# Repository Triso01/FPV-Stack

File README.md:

# My FPV Stack

Note:
  I made it because I want to learn how to make BLDC-ESCs, 
  Designing my own FPV Stack, it WILL have errors, so do NOT use it in your Drone!
  The 4 in 1 ESC will be continued later, I don not have the experience to finish it yet.
  
## Flight Controller:

- No Analog OSD, made for BetaFPV P1 or optionally Walksnail and DJI
- BEC: 5V 3A; 9V 3A
- IMU (Gyro): ICM-20602
- STM32F405
- Buzzer Pads
- 1 UART free to use e.g. for GPS

ESC and Flight Controller Connector Pinout:

| [1]  | [2] | [3]  | [4]  | [5] | [6] | [7] | [8] |
|------|-----|------|------|-----|-----|-----|-----|
| VBAT | GND | CUR  | TEL  | M1  | M2  | M3  | M4  |

VTX Connector Pinout:

| [1] | [2] | [3]  | [4]   | [5] | [6] |
|-----|-----|------|-------|-----|-----|
| 5V  | GND | U1_TX| U1_RX | GND | NC  |

## ESCs:
Based on EFM88B21, FD6288 and PSMN1R4-40YLDX.
  - Bluejay (Layout A), BLHeli_S compatible
  - Dshot bidirectional

## ESC distribution board:
10V Buck, 3,3V LDO and the ampmeter

[Will be finished, when I have more experience]:
4in1 ESC:
Based on EFM8BB21, FD6288Q and 24 PSMN1R4-40YLDX.
The PCB size is not final yet, it WILL change.
  - Bluejay (Laout A), BLHeli_S compatible
  - Dshot bidirectional compatible
  - Current Sensor: INA168 with a 0.5mOhms shunt
  - LMR14010 10V Buck to provide Gate voltage
  - AP2204K LDO 10V -> 3.3V
(You can see "pictures" when opening the PCB Files with KiCad)

## What are the boards for?

The Flight Controller (FC) is the main control board and the "brain" of the FPV stack. It runs the flight-control firmware and uses its IMU to measure the drone's movement, which is required for stable flight.

The ESC Distribution Board distributes one battery connection to four individual ESCs. It also generates the 10 V gate-driver supply, and measures the total battery current.

Each Electronic Speed Controller (ESC) drives one three-phase brushless motor. Designing this small, high-current board was the most challenging part of the project.

## Now the expensive things (duhhh):

PCBs:

Settings for FC:

Settings for ESC:

Settings for ESC-Distrib:

(You can change Surface Finish and Color if you want another Color or a higher quality finish)

Parts:
1. Select the columns like this
2. Click "Create BOM"

3. Click on "Add to Cart"

## Grouped BOM

| Part group | Qty used | Price (USD) |
|---|---:|---:|
| Resistors, including the current shunt | 68 | $3.09 |
| Capacitors | 85 | $9.99 |
| Inductors | 3 | $2.40 |
| Semiconductors and ICs | 57 | $73.05 |
| USB receptacle | 1 | $1.50 |
| Switches | 2 | $0.53 |
| Cables | 6 | $0.00 |
| PCBs | 6 | $103.30 |
| Shipping | 1-2 | ~$20-40 |
| **Total** | | **$195.79** |

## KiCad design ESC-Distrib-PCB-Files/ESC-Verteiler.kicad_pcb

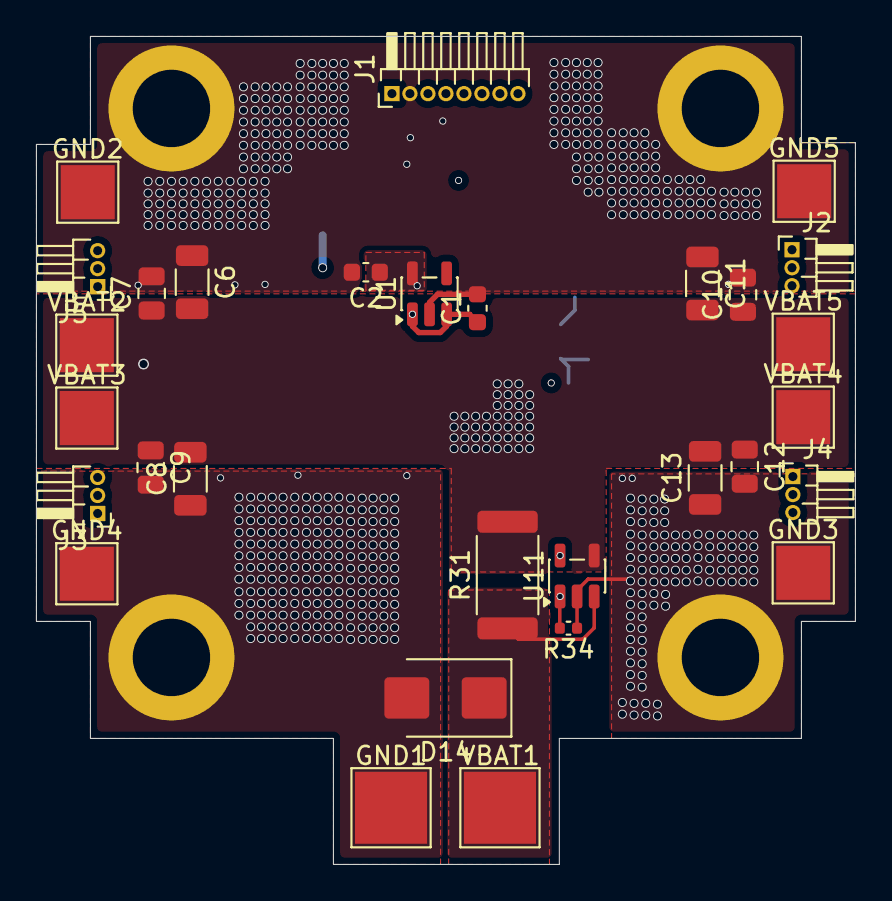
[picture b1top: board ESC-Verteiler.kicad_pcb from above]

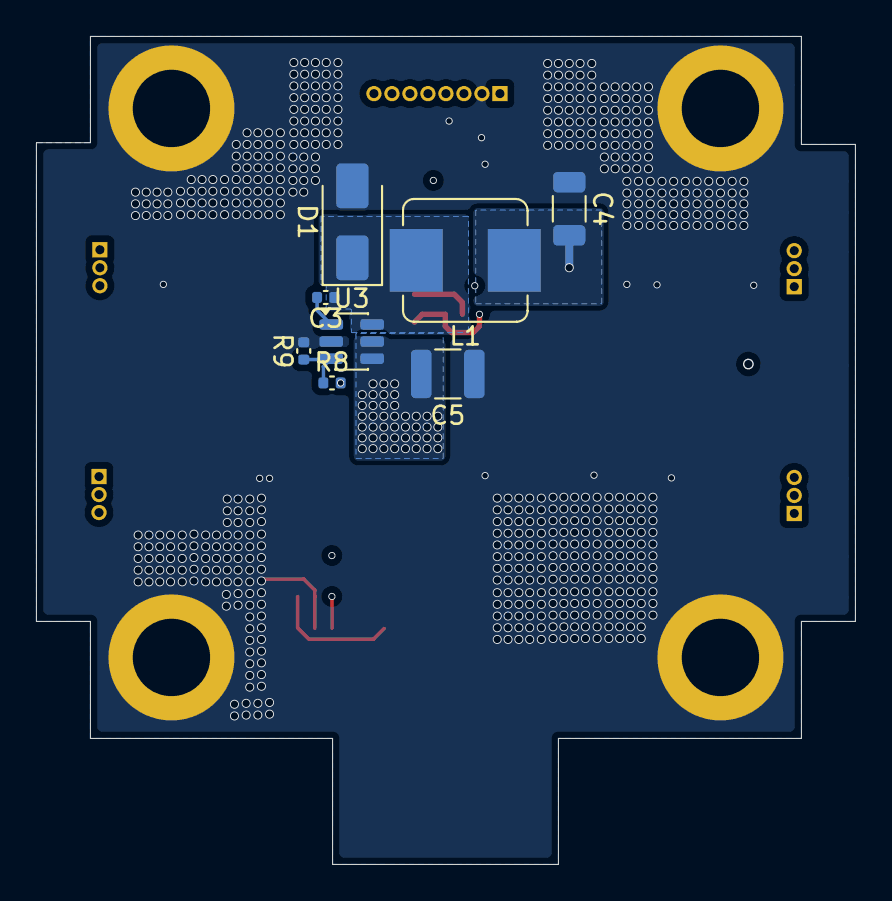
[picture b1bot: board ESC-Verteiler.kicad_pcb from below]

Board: 4 copper layers, 45.5 x 46.0 mm, 38 parts (8 on the bottom side), 13 nets.

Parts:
C1: 1uf; C_0603_1608Metric
C2: 2.2uf; C_0603_1608Metric
C3: 100nf; C_0402_1005Metric
C4: 22uf; C_1206_3216Metric
C5: 10uf; C_1210_3225Metric
C6, C8, C11, C13: 1uf; C_1206_3216Metric
C7, C9, C10, C12: 100nf; C_0805_2012Metric
D1: D; D_SMA
D14: D; D_SMB
GND1: TestPoint_Pad_4.0x4.0mm
GND2, GND3, GND4, GND5: TestPoint_Pad_3.0x3.0mm
J1: Conn_01x08_Socket; PinHeader_1x08_P1.00mm_Horizontal
J2, J3, J4, J5: Conn_01x03_Pin; PinHeader_1x03_P1.00mm_Horizontal
L1: 22uH; L_Bourns_SRP7028A_7.3x6.6mm
R8: 121kOhm; C_0402_1005Metric
R9: 10kOhm; C_0402_1005Metric
R31: 0.5mOhms; R_2512_6332Metric
R34: 200kOhm; C_0402_1005Metric
U1: AP2204K-3.3; SOT-23-5
U3: LMR14010ADDCT; SOT-23-6
U11: INA168; SOT-23-5
VBAT1: TestPoint_Pad_4.0x4.0mm
VBAT2, VBAT3, VBAT4, VBAT5: TestPoint_Pad_3.0x3.0mm

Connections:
/10V: C1.1, C4.2, J2.1, J3.3, J4.1, J5.3, L1.1, R8.2, U1.1 (VIN), U1.3 (EN)
/CUR: J1.3, R34.2, U11.1
/DSHOT_M1: J1.8, J3.2
/DSHOT_M2: J1.7, J5.2
/DSHOT_M3: J1.6, J2.2
/DSHOT_M4: J1.5, J4.2
/GND: C1.2, C2.2, C4.1, C5.1, C6.1, C7.2, C8.1, C9.2, C10.2, C11.1, C12.2, C13.1, D1.2 (A), D14.2 (A), GND1.1 (1_1), GND2.1 (1_1), GND3.1 (1_1), GND4.1 (1_1), GND5.1 (1_1), J1.2, R9.2, R34.1, U1.2 (GND), U3.2 (GND), U11.2 (GND)
/VBAT: C5.2, C6.2, C7.1, C8.2, C9.1, C10.1, C11.2, C12.1, C13.2, J1.1, R31.2, U3.4 (SHDN), U3.5 (VIN), U11.4 (-), VBAT2.1 (1_1), VBAT3.1 (1_1), VBAT4.1 (1_1), VBAT5.1 (1_1)
/VDD: C2.1, J2.3, J3.1, J4.3, J5.1, U1.5 (VOUT), U11.5 (V+)
unnamed: C3.1, D1.1 (K), L1.2, U3.6 (SW)
unnamed: D14.1 (K), R31.1, U11.3 (+), VBAT1.1 (1_1)
unnamed: C3.2, U3.1 (CB)
unnamed: R8.1, R9.1, U3.3 (FB)

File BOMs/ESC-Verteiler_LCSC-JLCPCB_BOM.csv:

"Comment","Designator","Footprint","Quantity","LCSC Part #"
"1uf","C1","Capacitor_SMD:C_0603_1608Metric","1","C15849"
"2.2uf","C2","Capacitor_SMD:C_0603_1608Metric","1","C23630"
"100nf","C3","Capacitor_SMD:C_0402_1005Metric","1","C960916"
"22uf","C4","Capacitor_SMD:C_1206_3216Metric","1","C2858005"
"10uf","C5","Capacitor_SMD:C_1210_3225Metric","1","C342670"
"1uf","C6,C8,C11,C13","Capacitor_SMD:C_1206_3216Metric","4","C1853626"
"100nf","C7,C9,C10,C12","Capacitor_SMD:C_0805_2012Metric","4","C1711"
"D","D1","Diode_SMD:D_SMA","1","C169419"
"D","D14","Diode_SMD:D_SMB","1","C726831"
"JST SH 1.0mm Horizontal 8P","J1","Connector_JST:JST_SH_SM08B-SRSS-TB_1x08-1MP_P1.00mm_Horizontal","1","C160407"
"JST SH 1.0mm Horizontal 3P","J2,J3,J4,J5","Connector_JST:JST_SH_SM03B-SRSS-TB_1x03-1MP_P1.00mm_Horizontal","4","C160403"
"22uH","L1","Inductor_SMD:L_Bourns_SRP7028A_7.3x6.6mm","1","C1330991"
"121kOhm","R8","Resistor_SMD:R_0402_1005Metric","1","C112303"
"10kOhm","R9","Resistor_SMD:R_0402_1005Metric","1","C25744"
"0.5mOhms","R31","Resistor_SMD:R_2512_6332Metric","1","C154666"
"200kOhm","R34","Resistor_SMD:R_0402_1005Metric","1","C25764"
"AP2204K-3.3","U1","Package_TO_SOT_SMD:SOT-23-5","1","C112032"
"LMR14010ADDCT","U3","Package_TO_SOT_SMD:TSOT-23-6","1","C2070867"
"INA168","U11","Package_TO_SOT_SMD:SOT-23-5","1","C134294"

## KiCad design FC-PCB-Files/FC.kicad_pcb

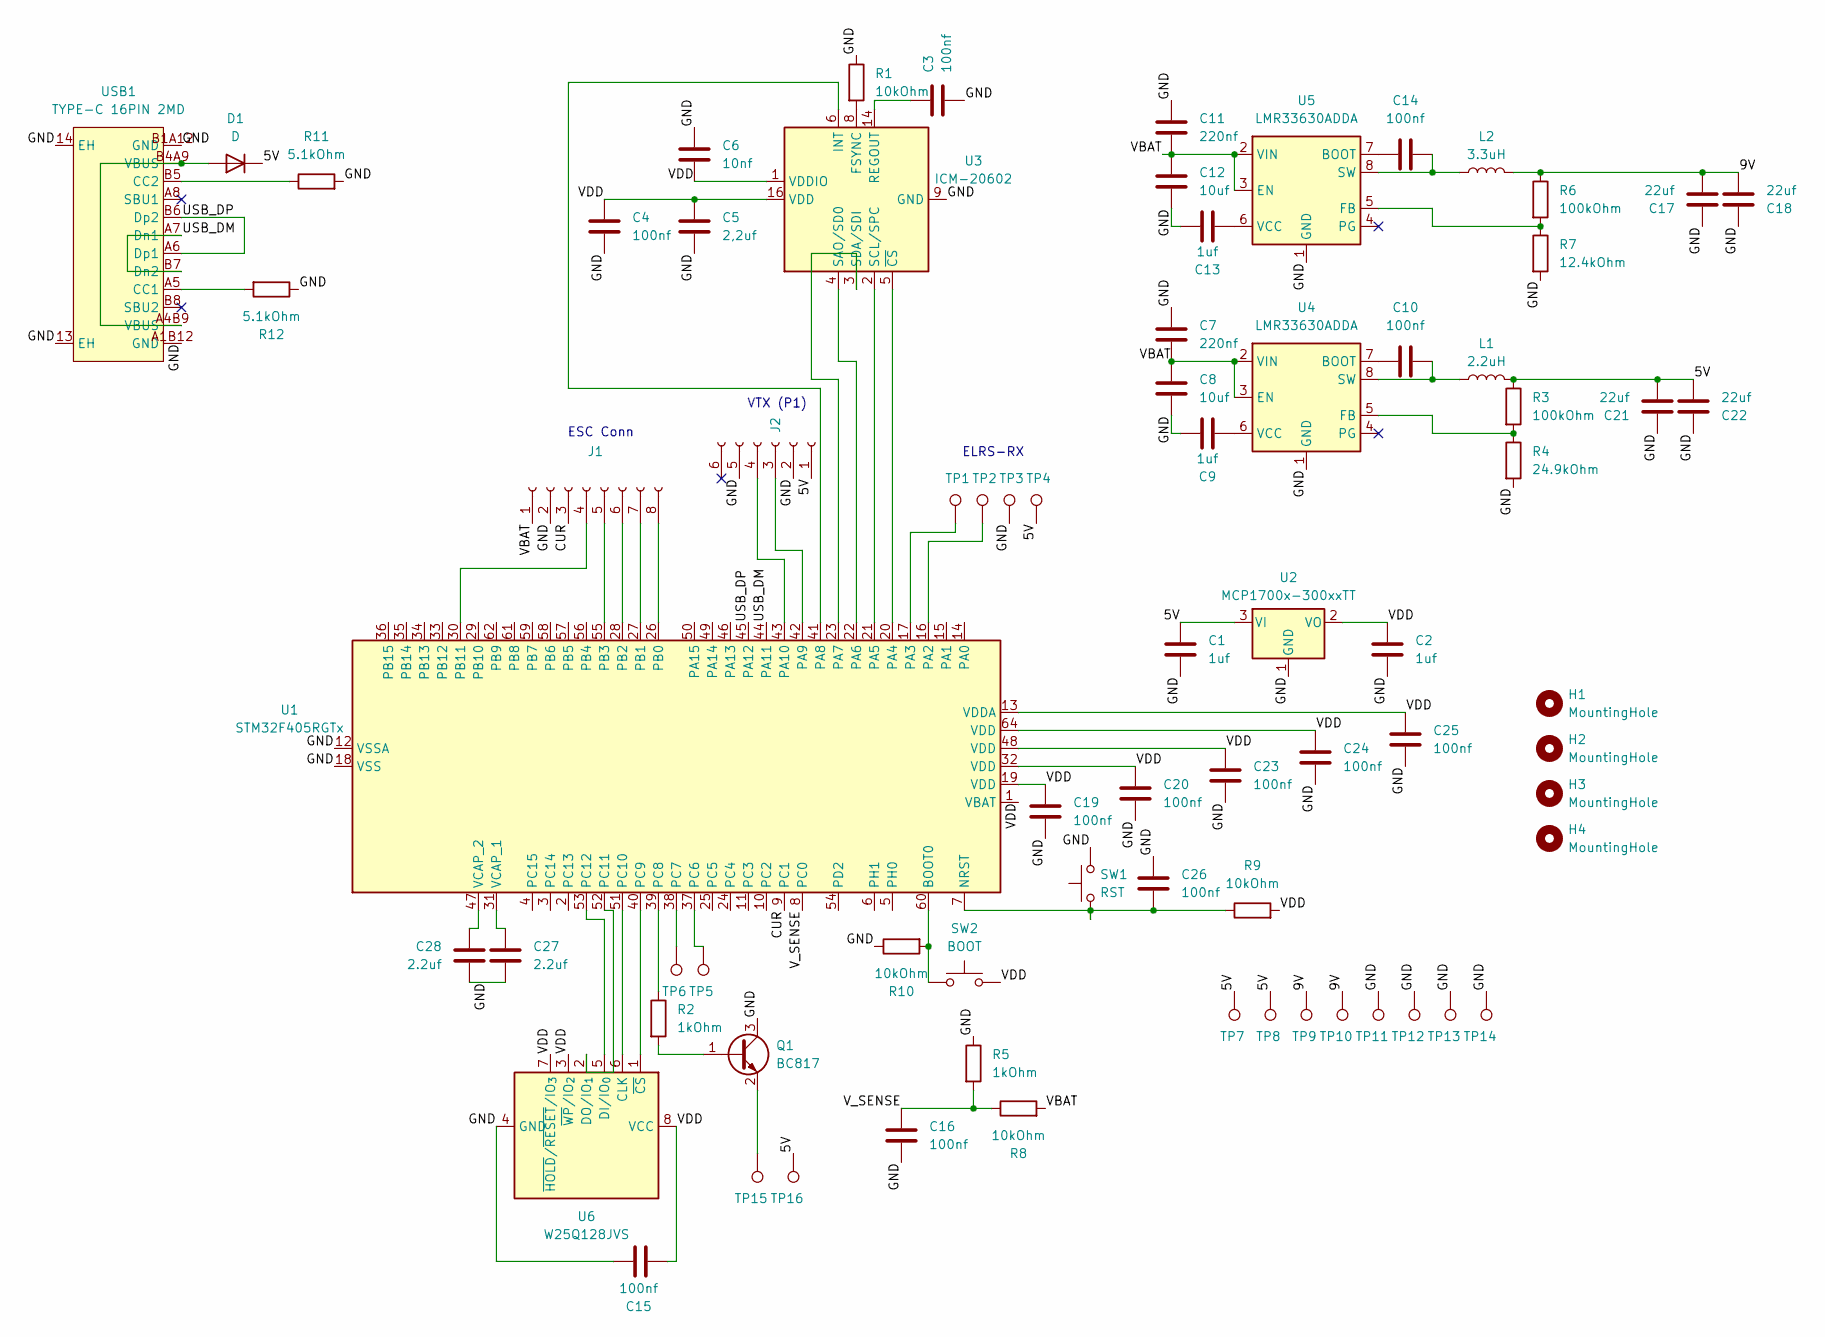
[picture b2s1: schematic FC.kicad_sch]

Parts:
C1, C2, C9, C13: 1uf; C_0402_1005Metric_Pad0.74x0.62mm_HandSolder
C3, C4, C10, C14, C15, C16, C19, C20, C23, C24, C25, C26: 100nf; C_0402_1005Metric_Pad0.74x0.62mm_HandSolder
C5: 2,2uf; C_0402_1005Metric_Pad0.74x0.62mm_HandSolder
C6: 10nf; C_0402_1005Metric_Pad0.74x0.62mm_HandSolder
C7, C11: 220nf; C_0402_1005Metric_Pad0.74x0.62mm_HandSolder
C8, C12: 10uf; C_0805_2012Metric
C17, C18, C21, C22: 22uf; C_0603_1608Metric_Pad1.08x0.95mm_HandSolder
C27, C28: 2.2uf; C_0402_1005Metric_Pad0.74x0.62mm_HandSolder
D1: D; D_SOD-123
H1, H2, H3, H4: MountingHole; MountingHole_4.3mm_M4_DIN965_Pad_TopOnly
J1: Conn_01x08_Socket; PinHeader_1x08_P1.00mm_Horizontal
J2: Conn_01x06_Socket; PinHeader_1x06_P1.00mm_Horizontal
L1: 2.2uH; L_APV_ANR3015
L2: 3.3uH; L_APV_ANR3015
Q1: BC817; SOT-23
R1, R8, R9, R10: 10kOhm; R_0402_1005Metric_Pad0.72x0.64mm_HandSolder
R2, R5: 1kOhm; R_0402_1005Metric_Pad0.72x0.64mm_HandSolder
R3, R6: 100kOhm; R_0402_1005Metric_Pad0.72x0.64mm_HandSolder
R4: 24.9kOhm; R_0402_1005Metric_Pad0.72x0.64mm_HandSolder
R7: 12.4kOhm; R_0402_1005Metric_Pad0.72x0.64mm_HandSolder
R11, R12: 5.1kOhm; R_0402_1005Metric_Pad0.72x0.64mm_HandSolder
SW1: RST; SW-SMD_L3.9-W3.0-P4.45
SW2: BOOT; SW-SMD_L3.9-W3.0-P4.45
TP1, TP2, TP3, TP4, TP5, TP6, TP7, TP8, TP9, TP10, TP11, TP12, TP13, TP14, TP15, TP16: TestPoint; TestPoint_Pad_D1.5mm
U1: STM32F405RGTx; LQFP-64_10x10mm_P0.5mm
U2: MCP1700x-300xxTT; SOT-23
U3: ICM-20602; LGA-16_3x3mm_P0.5mm_LayoutBorder3x5y
U4, U5: LMR33630ADDA; Texas_HSOP-8-1EP_3.9x4.9mm_P1.27mm_ThermalVias
U6: W25Q128JVS; SOIC-8_5.3x5.3mm_P1.27mm
USB1: TYPE-C 16PIN 2MD; USB-C-SMD_TYPE-C-16PIN-2MD-073; MPN TYPE-C 16PIN 2MD(073); LCSC Part C2765186

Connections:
/5V: C1.1, C21.2, C22.2, D1.1 (K), J2.1, L1.2, R3.1, TP4.1 (1_1), TP7.1 (1_1), TP8.1 (1_1), TP16.1 (1_1), U2.3 (VI)
/9V: C17.2, C18.2, L2.2, R6.1, TP9.1 (1_1), TP10.1 (1_1)
/CUR: J1.3, U1.9 (PC1)
/GND: C1.2, C2.2, C3.2, C4.2, C5.2, C6.1, C7.1, C8.2, C9.2, C11.1, C12.2, C13.2, C15.2, C16.2, C17.1, C18.1, C19.2, C20.2, C21.1, C22.1, C23.2, C24.2, C25.2, C26.1, C27.2, C28.2, J1.2, J2.2, J2.5, Q1.3 (C), R1.1, R4.2, R5.1, R7.2, R10.1, R11.2, R12.1, SW1.2, TP3.1 (1_1), TP11.1 (1_1), TP12.1 (1_1), TP13.1 (1_1), TP14.1 (1_1), U1.12 (VSSA), U1.18 (VSS), U1.63 (VSS), U2.1 (GND), U3.9 (GND), U3.10 (GND), U3.11 (GND), U3.12 (GND), U3.13 (GND), U3.15 (GND), U4.1 (GND), U4.9 (GND), U5.1 (GND), U5.9 (GND), U6.4 (GND), USB1.13 (EH), USB1.14 (EH), USB1.A1B12 (GND), USB1.B1A12 (GND)
/USB_DM: U1.44 (PA11), USB1.A7 (Dn1), USB1.B7 (Dn2)
/USB_DP: U1.45 (PA12), USB1.A6 (Dp1), USB1.B6 (Dp2)
/VBAT: C7.2, C8.1, C11.2, C12.1, J1.1, R8.2, U4.2 (VIN), U4.3 (EN), U5.2 (VIN), U5.3 (EN)
/VDD: C2.1, C4.1, C5.1, C6.2, C15.1, C19.1, C20.1, C23.1, C24.1, C25.1, R9.2, SW2.2, U1.1 (VBAT), U1.13 (VDDA), U1.19 (VDD), U1.32 (VDD), U1.48 (VDD), U1.64 (VDD), U2.2 (VO), U3.1 (VDDIO), U3.16 (VDD), U6.3 (~WP/IO_{2}), U6.7 (~HOLD/~RESET/IO_{3}), U6.8 (VCC)
/V_SENSE: C16.1, R5.2, R8.1, U1.8 (PC0)
unnamed: D1.2 (A), USB1.A4B9 (VBUS), USB1.B4A9 (VBUS)
unnamed: J1.4, U1.30 (PB11)
unnamed: J1.5, U1.55 (PB3)
unnamed: J1.6, U1.28 (PB2)
unnamed: J1.7, U1.27 (PB1)
unnamed: J1.8, U1.26 (PB0)
unnamed: J2.3, U1.42 (PA9)
unnamed: J2.4, U1.43 (PA10)
unnamed: Q1.1 (B), R2.2
unnamed: Q1.2 (E), TP15.1 (1_1)
unnamed: R10.2, SW2.1, U1.60 (BOOT0)
unnamed: C26.2, R9.1, SW1.1, U1.7 (NRST)
unnamed: TP2.1 (1_1), U1.16 (PA2)
unnamed: TP1.1 (1_1), U1.17 (PA3)
unnamed: U1.20 (PA4), U3.5 (~CS)
unnamed: U1.21 (PA5), U3.2 (SCL/SPC)
unnamed: U1.22 (PA6), U3.4 (SAO/SD0)
unnamed: U1.23 (PA7), U3.3 (SDA/SDI)
unnamed: U1.41 (PA8), U3.6 (INT)
unnamed: TP5.1 (1_1), U1.37 (PC6)
unnamed: TP6.1 (1_1), U1.38 (PC7)
unnamed: R2.1, U1.39 (PC8)
unnamed: U1.40 (PC9), U6.1 (~CS)
unnamed: U1.51 (PC10), U6.6 (CLK)
unnamed: U1.52 (PC11), U6.2 (DO/IO_{1})
unnamed: U1.53 (PC12), U6.5 (DI/IO_{0})
unnamed: C27.1, U1.31 (VCAP_1)
unnamed: C28.1, U1.47 (VCAP_2)
unnamed: R1.2, U3.8 (FSYNC)
unnamed: C3.1, U3.14 (REGOUT)
unnamed: C10.1, U4.7 (BOOT)
unnamed: R3.2, R4.1, U4.5 (FB)
unnamed: C10.2, L1.1, U4.8 (SW)
unnamed: C9.1, U4.6 (VCC)
unnamed: C14.1, U5.7 (BOOT)
unnamed: R6.2, R7.1, U5.5 (FB)
unnamed: C14.2, L2.1, U5.8 (SW)
unnamed: C13.1, U5.6 (VCC)
unnamed: R12.2, USB1.A5 (CC1)
unnamed: R11.1, USB1.B5 (CC2)

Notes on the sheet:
VTX (P1)
ELRS-RX
ESC Conn

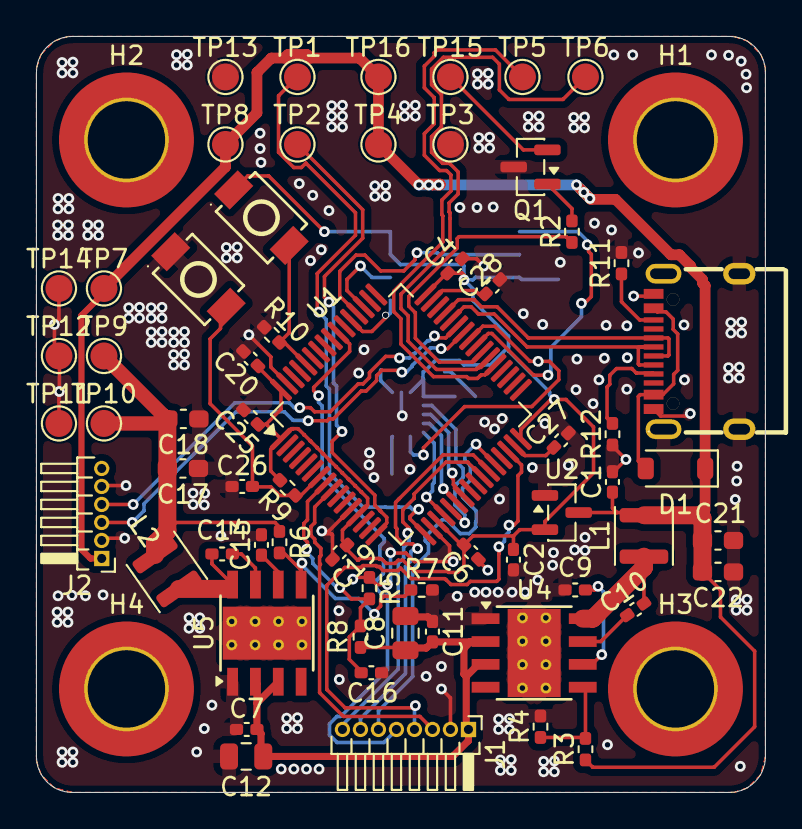
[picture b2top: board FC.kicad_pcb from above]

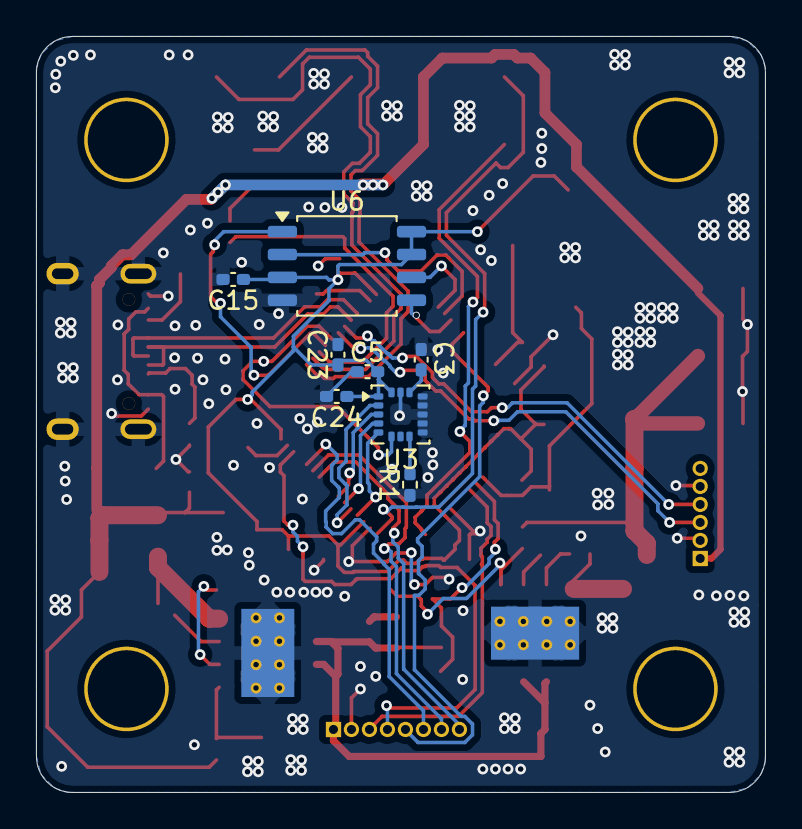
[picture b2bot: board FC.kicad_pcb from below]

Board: 2 copper layers, 40.5 x 42.0 mm, 75 parts (8 on the bottom side), 49 nets.

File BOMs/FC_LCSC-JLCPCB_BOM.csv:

"Comment","Designator","Footprint","Quantity","LCSC Part #"
"1uf","C1,C2,C9,C13","Capacitor_SMD:C_0402_1005Metric_Pad0.74x0.62mm_HandSolder","4","C52923"
"100nf","C3,C4,C10,C14,C15,C16,C19,C20,C23,C24,C25,C26","Capacitor_SMD:C_0402_1005Metric_Pad0.74x0.62mm_HandSolder","12","C960916"
"2.2uF","C5,C27,C28","Capacitor_SMD:C_0402_1005Metric_Pad0.74x0.62mm_HandSolder","3","C5119302"
"10nf","C6","Capacitor_SMD:C_0402_1005Metric_Pad0.74x0.62mm_HandSolder","1","C15195"
"220nf","C7,C11","Capacitor_SMD:C_0402_1005Metric_Pad0.74x0.62mm_HandSolder","2","C5159775"
"10uf","C8,C12","Capacitor_SMD:C_1210_3225Metric","2","C342670"
"22uf","C17,C18,C21,C22","Capacitor_SMD:C_0603_1608Metric_Pad1.08x0.95mm_HandSolder","4","C2762594"
"D","D1","Diode_SMD:D_SOD-123","1","C82544"
"JST SH 1.0mm Horizontal 8P","J1","Connector_JST:JST_SH_SM08B-SRSS-TB_1x08-1MP_P1.00mm_Horizontal","1","C160407"
"JST SH 1.0mm Horizontal 6P","J2","Connector_JST:JST_SH_SM06B-SRSS-TB_1x06-1MP_P1.00mm_Horizontal","1","C160405"
"2.2uH","L1","Inductor_SMD:L_APV_ANR3015","1","C6364793"
"3.3uH","L2","Inductor_SMD:L_APV_ANR3015","1","C7427087"
"BC817","Q1","Package_TO_SOT_SMD:SOT-23","1","C181151"
"10kOhm","R1,R8,R9,R10","Resistor_SMD:R_0402_1005Metric_Pad0.72x0.64mm_HandSolder","4","C25744"
"1kOhm","R2,R5","Resistor_SMD:R_0402_1005Metric_Pad0.72x0.64mm_HandSolder","2","C11702"
"100kOhm","R3,R6","Resistor_SMD:R_0402_1005Metric_Pad0.72x0.64mm_HandSolder","2","C25741"
"24.9kOhm","R4","Resistor_SMD:R_0402_1005Metric_Pad0.72x0.64mm_HandSolder","1","C25874"
"12.4kOhm","R7","Resistor_SMD:R_0402_1005Metric_Pad0.72x0.64mm_HandSolder","1","C11692"
"5.1kOhm","R11,R12","Resistor_SMD:R_0402_1005Metric_Pad0.72x0.64mm_HandSolder","2","C25905"
"Taster (RST/BOOT)","SW1,SW2","EasyEDA:SW-SMD_L3.9-W3.0-P4.45","2","C720477"
"STM32F405RGTx","U1","Package_QFP:LQFP-64_10x10mm_P0.5mm","1","C15742"
"MCP1700x-300xxTT","U2","Package_TO_SOT_SMD:SOT-23","1","C62244"
"ICM-20602","U3","Package_LGA:LGA-16_3x3mm_P0.5mm_LayoutBorder3x5y","1","C97633"
"LMR33630ADDA","U4,U5","Package_SO:Texas_HSOP-8-1EP_3.9x4.9mm_P1.27mm_ThermalVias","2","C841384"
"W25Q128JVS","U6","Package_SO:SOIC-8_5.3x5.3mm_P1.27mm","1","C113767"
"TYPE-C 16PIN 2MD","USB1","EasyEDA:USB-C-SMD_TYPE-C-16PIN-2MD-073","1","C2765186"

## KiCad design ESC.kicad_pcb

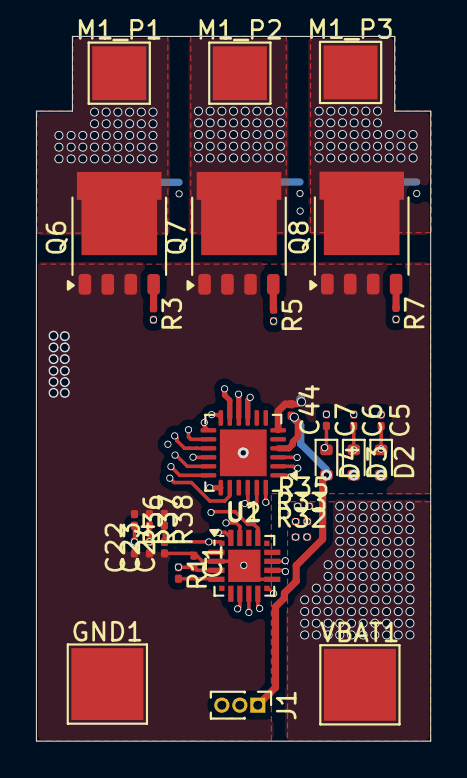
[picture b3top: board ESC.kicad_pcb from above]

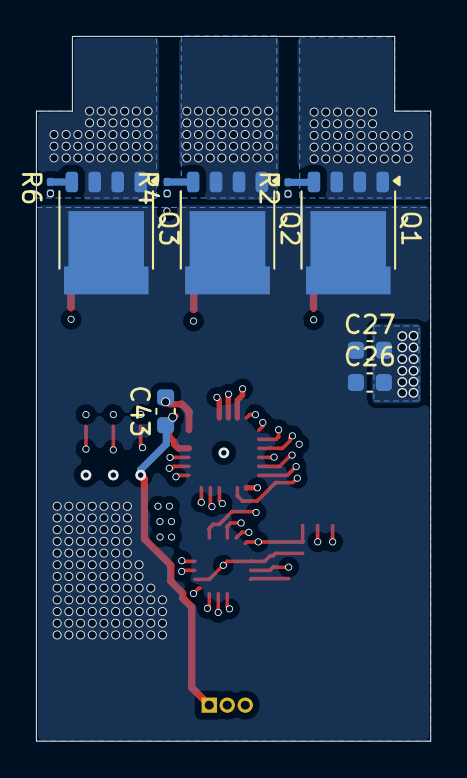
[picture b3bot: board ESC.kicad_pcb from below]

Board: 4 copper layers, 21.9 x 39.1 mm, 41 parts (9 on the bottom side), 33 nets.

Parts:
C1, C5, C6, C7, C44: 100nf; C_0201_0603Metric
C22, C23, C24: 1nf; C_0201_0603Metric
C26, C43: 1uf; C_0603_1608Metric
C27: 100nf; C_0603_1608Metric
D2, D3, D4: BAT54; D_SOD-523
GND1: TestPoint; TestPoint_Pad_4.0x4.0mm
J1: Conn_01x03_Socket; PinHeader_1x03_P1.00mm_Vertical
M1_P1, M1_P2, M1_P3: TestPoint; TestPoint_Pad_3.0x3.0mm
Q1, Q2, Q3, Q6, Q7, Q8: PSMN1R4-40YLDX; LFPAK56
R1, R36, R37, R38: 10kOhm; R_0201_0603Metric
R2, R3, R4, R5, R6, R7: 10Ohm; R_0201_0603Metric
R32, R33, R35: 100kOhm; R_0201_0603Metric
U1: EFM8BB21F16G-C-QFN20R; SiliconLabs_QFN-20-1EP_3x3mm_P0.5mm_EP1.8x1.8mm
U2: FD6288Q; HVQFN-24-1EP_4x4mm_P0.5mm_EP2.6x2.6mm
VBAT1: TestPoint; TestPoint_Pad_4.0x4.0mm

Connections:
/10V: C43.1, C44.2, D2.2 (A), D3.2 (A), D4.2 (A), J1.1, U2.4 (VCC)
/DSHOT: J1.2, U1.17 (P0.5)
/GND: C1.1, C22.1, C23.1, C24.1, C26.2, C27.2, C43.2, C44.1, GND1.1 (1_1), Q6.1 (S_1), Q6.2 (S_2), Q6.3 (S_3), Q7.1 (S_1), Q7.2 (S_2), Q7.3 (S_3), Q8.1 (S_1), Q8.2 (S_2), Q8.3 (S_3), R36.1, R37.1, R38.1, U1.3 (GND), U1.12 (GND), U1.21 (GND), U2.6 (COM), U2.25 (EXP)
/VBAT: C26.1, C27.1, Q1.5 (D_1), Q2.5 (D_1), Q3.5 (D_1), VBAT1.1 (1_1)
/VDD: C1.2, J1.3, R1.1, U1.4 (VDD)
/VS1_M1: C5.1, M1_P1.1 (1_1), Q1.1 (S_1), Q1.2 (S_2), Q1.3 (S_3), Q6.5 (D_1), R32.2, U2.18 (VS1)
/VS2_M1: C6.1, M1_P2.1 (1_1), Q2.1 (S_1), Q2.2 (S_2), Q2.3 (S_3), Q7.5 (D_1), R33.2, U2.15 (VS2)
/VS3_M1: C7.1, M1_P3.1 (1_1), Q3.1 (S_1), Q3.2 (S_2), Q3.3 (S_3), Q8.5 (D_1), R35.2, U2.12 (VS3)
unnamed: C5.2, D2.1 (K), U2.20 (VB1)
unnamed: C6.2, D3.1 (K), U2.17 (VB2)
unnamed: C7.2, D4.1 (K), U2.14 (VB3)
unnamed: Q1.4 (G), R2.2
unnamed: Q2.4 (G), R4.2
unnamed: Q3.4 (G), R6.2
unnamed: Q6.4 (G), R3.1
unnamed: Q7.4 (G), R5.1
unnamed: Q8.4 (G), R7.1
unnamed: C24.2, R32.1, R38.2, U1.1 (P0.1)
unnamed: C23.2, R33.1, R37.2, U1.20 (P0.2)
unnamed: C22.2, R35.1, R36.2, U1.19 (P0.3)
unnamed: U1.14 (P1.0), U2.22 (HIN1)
unnamed: U1.13 (P1.1), U2.1 (LIN1)
unnamed: U1.11 (P1.2), U2.23 (HIN2)
unnamed: U1.10 (P1.3), U2.2 (LIN2)
unnamed: U1.9 (P1.4), U2.24 (HIN3)
unnamed: U1.8 (P1.5), U2.3 (LIN3)
unnamed: R1.2, U1.5 (RSTb/C2CK)
unnamed: R2.1, U2.19 (HO1)
unnamed: R4.1, U2.16 (HO2)
unnamed: R6.1, U2.13 (HO3)
unnamed: R3.2, U2.11 (LO1)
unnamed: R5.2, U2.10 (LO2)
unnamed: R7.2, U2.9 (LO3)

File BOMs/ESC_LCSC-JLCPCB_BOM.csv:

"Comment","Designator","Footprint","Quantity","LCSC Part #"
"100nf","C1,C5,C6,C7,C44","Capacitor_SMD:C_0201_0603Metric","5","C2903663"
"1nf","C22,C23,C24","Capacitor_SMD:C_0201_0603Metric","3","C2874741"
"1uf","C26,C43","Capacitor_SMD:C_0603_1608Metric","2","C15849"
"100nf","C27","Capacitor_SMD:C_0603_1608Metric","1","C1591"
"BAT54","D2,D3,D4","Diode_SMD:D_SOD-523","3","C283259"
"JST SH 1.0mm Horizontal 3P","J1","Connector_JST:JST_SH_SM03B-SRSS-TB_1x03-1MP_P1.00mm_Horizontal","1","C160403"
"PSMN1R4-40YLDX","Q1,Q2,Q3,Q6,Q7,Q8","Package_TO_SOT_SMD:LFPAK56","6","C458253"
"10kOhm","R1,R36,R37,R38","Resistor_SMD:R_0201_0603Metric","4","C473048"
"10Ohm","R2,R3,R4,R5,R6,R7","Resistor_SMD:R_0201_0603Metric","6","C105901"
"100kOhm","R32,R33,R35","Resistor_SMD:R_0201_0603Metric","3","C270364"
"EFM8BB21F16G-C-QFN20R","U1","Package_DFN_QFN:SiliconLabs_QFN-20-1EP_3x3mm_P0.5mm_EP1.8x1.8mm","1","C80713"
"FD6288Q","U2","Package_DFN_QFN:HVQFN-24-1EP_4x4mm_P0.5mm_EP2.6x2.6mm","1","C328453"

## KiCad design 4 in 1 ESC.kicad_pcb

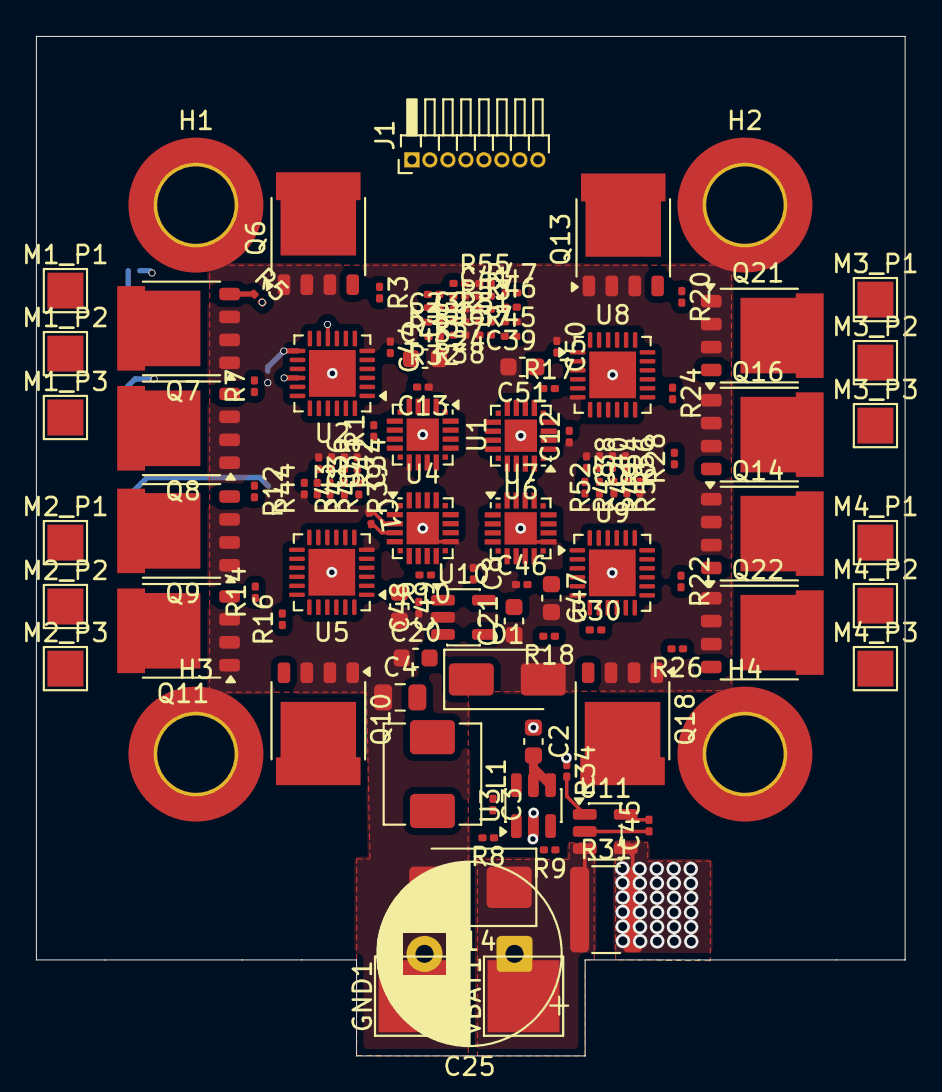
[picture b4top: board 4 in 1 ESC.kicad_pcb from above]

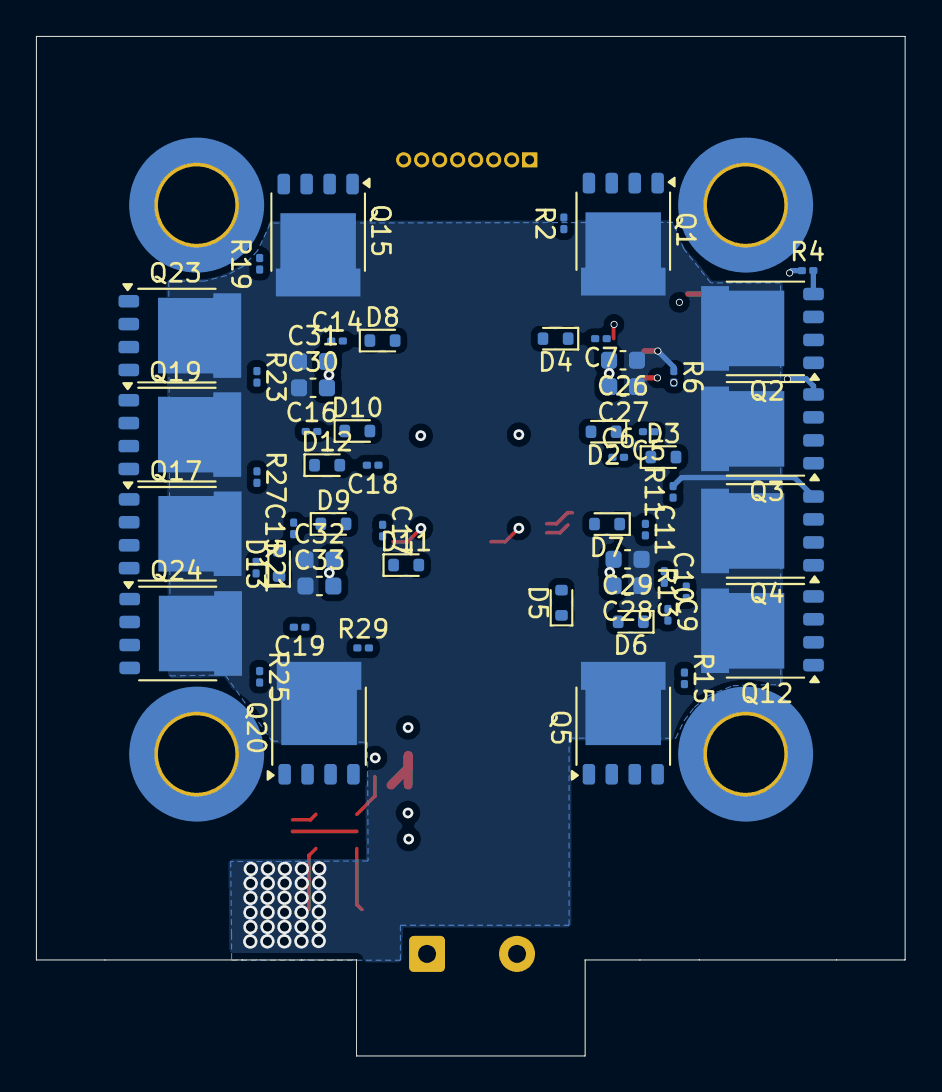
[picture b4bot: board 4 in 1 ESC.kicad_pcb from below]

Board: 4 copper layers, 48.3 x 56.6 mm, 176 parts (56 on the bottom side), 125 nets.

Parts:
C1, C3, C5, C6, C7, C8, C9, C10, C11, C12, C13, C14, C15, C16, C17, C18, C19, C44, C45, C46, C48, C50: 100nf; C_0201_0603Metric
C2: 10uf; C_0603_1608Metric
C4: 22uf; C_0805_2012Metric
C20, C26, C28, C30, C32, C43, C47, C49, C51: 1uf; C_0603_1608Metric
C21: 2.2uf; C_0603_1608Metric
C22, C23, C24, C34, C35, C36, C37, C38, C39, C40, C41, C42: 1nf; C_0201_0603Metric
C25: 470uf; CP_Radial_D10.0mm_P5.00mm
C27, C29, C31, C33: 100nf; C_0603_1608Metric
D1: D; D_SMA
D2, D3, D4, D5, D6, D7, D8, D9, D10, D11, D12, D13: BAT54; D_SOD-523
D14: D; D_SMB
GND1: TestPoint_Pad_4.0x4.0mm
H1, H2, H3, H4: MountingHole_Pad; MountingHole_4.3mm_M4_DIN965_Pad_TopBottom
J1: Conn_01x08_Socket; PinHeader_1x08_P1.00mm_Horizontal
L1: 22uH; L_Sunlord_MWSA0503S
M1_P1, M1_P2, M1_P3, M2_P1, M2_P2, M2_P3, M3_P1, M3_P2, M3_P3, M4_P1, M4_P2, M4_P3: TestPoint; TestPoint_Pad_2.0x2.0mm
Q1, Q2, Q3, Q4, Q5, Q6, Q7, Q8, Q9, Q10, Q11, Q12, Q13, Q14, Q15, Q16, Q17, Q18, Q19, Q20, Q21, Q22, Q23, Q24: PSMN1R4-40YLDX; LFPAK56
R1, R9, R10, R17, R18, R36, R37, R38, R42, R43, R44, R51, R52, R53, R54, R55, R56: 10kOhm; R_0201_0603Metric
R2, R3, R4, R5, R6, R7, R11, R12, R13, R14, R15, R16, R19, R20, R21, R22, R23, R24, R25, R26, R27, R28, R29, R30: 10Ohm; R_0201_0603Metric
R8: 121kOhm; R_0201_0603Metric
R31: 0.5mOhms; R_1218_3246Metric
R32, R33, R35, R39, R40, R41, R45, R46, R47, R48, R49, R50: 100kOhm; R_0201_0603Metric
R34: 200kOhm; R_0201_0603Metric
U1, U4, U6, U7: EFM8BB21F16G-C-QFN20R; SiliconLabs_QFN-20-1EP_3x3mm_P0.5mm_EP1.8x1.8mm
U2, U5, U8, U9: FD6288Q; HVQFN-24-1EP_4x4mm_P0.5mm_EP2.6x2.6mm
U3: LMR14010ADDCT; TSOT-23-6
U10: AP2204K-3.3; SOT-23-5
U11: INA168; SOT-23-5
VBAT1: TestPoint_Pad_4.0x4.0mm

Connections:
/10V: C4.2, C20.2, C43.1, C44.2, C46.2, C47.1, C48.2, C49.1, C50.2, C51.1, D2.2 (A), D3.2 (A), D4.2 (A), D5.2 (A), D6.2 (A), D7.2 (A), D8.2 (A), D9.2 (A), D10.2 (A), D11.2 (A), D12.2 (A), D13.2 (A), L1.1, R8.2, U2.4 (VCC), U5.4 (VCC), U8.4 (VCC), U9.4 (VCC), U10.1 (VIN), U10.3 (EN)
/CUR: J1.3, R34.2, U11.1
/DSHOT_M1: J1.5, U1.17 (P0.5)
/DSHOT_M2: J1.6, U4.17 (P0.5)
/DSHOT_M3: J1.7, U6.17 (P0.5)
/DSHOT_M4: J1.8, U7.17 (P0.5)
/GND: C1.1, C2.1, C4.1, C8.1, C12.1, C13.1, C20.1, C21.1, C22.1, C23.1, C24.1, C25.2, C26.2, C27.2, C28.2, C29.2, C30.2, C31.2, C32.2, C33.2, C34.1, C35.1, C36.1, C37.1, C38.1, C39.1, C40.1, C41.1, C42.1, C43.2, C44.1, C45.1, C46.1, C47.2, C48.1, C49.2, C50.1, C51.2, D1.2 (A), D14.2 (A), GND1.1 (1_1), H1.1 (1_1), H2.1 (1_1), H3.1 (1_1), H4.1 (1_1), J1.2, Q6.1 (S_1), Q6.2 (S_2), Q6.3 (S_3), Q7.1 (S_1), Q7.2 (S_2), Q7.3 (S_3), Q8.1 (S_1), Q8.2 (S_2), Q8.3 (S_3), Q9.1 (S_1), Q9.2 (S_2), Q9.3 (S_3), Q10.1 (S_1), Q10.2 (S_2), Q10.3 (S_3), Q11.1 (S_1), Q11.2 (S_2), Q11.3 (S_3), Q13.1 (S_1), Q13.2 (S_2), Q13.3 (S_3), Q14.1 (S_1), Q14.2 (S_2), Q14.3 (S_3), Q16.1 (S_1), Q16.2 (S_2), Q16.3 (S_3), Q18.1 (S_1), Q18.2 (S_2), Q18.3 (S_3), Q21.1 (S_1), Q21.2 (S_2), Q21.3 (S_3), Q22.1 (S_1), Q22.2 (S_2), Q22.3 (S_3), R9.2, R34.1, R36.1, R37.1, R38.1, R42.1, R43.1, R44.1, R51.1, R52.1, R53.1, R54.1, R55.1, R56.1, U1.3 (GND), U1.12 (GND), U1.21 (GND), U2.6 (COM), U2.25 (EXP), U3.2 (GND), U4.3 (GND), U4.12 (GND), U4.21 (GND), U5.6 (COM), U5.25 (EXP), U6.3 (GND), U6.12 (GND), U6.21 (GND), U7.3 (GND), U7.12 (GND), U7.21 (GND), U8.6 (COM), U8.25 (EXP), U9.6 (COM), U9.25 (EXP), U10.2 (GND), U11.2 (GND)
/VBAT: C2.2, C26.1, C27.1, C28.1, C29.1, C30.1, C31.1, C32.1, C33.1, J1.1, Q1.5 (D_1), Q2.5 (D_1), Q3.5 (D_1), Q4.5 (D_1), Q5.5 (D_1), Q12.5 (D_1), Q15.5 (D_1), Q17.5 (D_1), Q19.5 (D_1), Q20.5 (D_1), Q23.5 (D_1), Q24.5 (D_1), R31.2, U3.4 (SHDN), U3.5 (VIN), U11.4 (-)
/VDD: C1.2, C8.2, C12.2, C13.2, C21.2, C45.2, R1.1, R10.1, R17.1, R18.1, U1.4 (VDD), U4.4 (VDD), U6.4 (VDD), U7.4 (VDD), U10.5 (VOUT), U11.5 (V+)
/VS1_M1: C5.1, M1_P1.1 (1_1), Q1.1 (S_1), Q1.2 (S_2), Q1.3 (S_3), Q6.5 (D_1), R32.2, U2.18 (VS1)
/VS1_M2: C9.1, M2_P1.1 (1_1), Q4.1 (S_1), Q4.2 (S_2), Q4.3 (S_3), Q9.5 (D_1), R41.2, U5.18 (VS1)
/VS1_M3: C14.1, M3_P1.1 (1_1), Q13.5 (D_1), Q15.1 (S_1), Q15.2 (S_2), Q15.3 (S_3), R47.2, U8.18 (VS1)
/VS1_M4: C15.1, M4_P1.1 (1_1), Q14.5 (D_1), Q17.1 (S_1), Q17.2 (S_2), Q17.3 (S_3), R50.2, U9.18 (VS1)
/VS2_M1: C6.1, M1_P2.1 (1_1), Q2.1 (S_1), Q2.2 (S_2), Q2.3 (S_3), Q7.5 (D_1), R33.2, U2.15 (VS2)
/VS2_M2: C10.1, M2_P2.1 (1_1), Q11.5 (D_1), Q12.1 (S_1), Q12.2 (S_2), Q12.3 (S_3), R40.2, U5.15 (VS2)
/VS2_M3: C16.1, M3_P2.1 (1_1), Q21.5 (D_1), Q23.1 (S_1), Q23.2 (S_2), Q23.3 (S_3), R46.2, U8.15 (VS2)
/VS2_M4: C17.1, M4_P2.1 (1_1), Q22.5 (D_1), Q24.1 (S_1), Q24.2 (S_2), Q24.3 (S_3), R49.2, U9.15 (VS2)
/VS3_M1: C7.1, M1_P3.1 (1_1), Q3.1 (S_1), Q3.2 (S_2), Q3.3 (S_3), Q8.5 (D_1), R35.2, U2.12 (VS3)
/VS3_M2: C11.1, M2_P3.1 (1_1), Q5.1 (S_1), Q5.2 (S_2), Q5.3 (S_3), Q10.5 (D_1), R39.2, U5.12 (VS3)
/VS3_M3: C18.1, M3_P3.1 (1_1), Q16.5 (D_1), Q19.1 (S_1), Q19.2 (S_2), Q19.3 (S_3), R45.2, U8.12 (VS3)
/VS3_M4: C19.1, M4_P3.1 (1_1), Q18.5 (D_1), Q20.1 (S_1), Q20.2 (S_2), Q20.3 (S_3), R48.2, U9.12 (VS3)
unnamed: C3.1, D1.1 (K), L1.2, U3.6 (SW)
unnamed: C5.2, D2.1 (K), U2.20 (VB1)
unnamed: C6.2, D3.1 (K), U2.17 (VB2)
unnamed: C7.2, D4.1 (K), U2.14 (VB3)
unnamed: C9.2, D5.1 (K), U5.20 (VB1)
unnamed: C10.2, D6.1 (K), U5.17 (VB2)
unnamed: C11.2, D7.1 (K), U5.14 (VB3)
unnamed: C14.2, D8.1 (K), U8.20 (VB1)
unnamed: C15.2, D9.1 (K), U9.20 (VB1)
unnamed: C16.2, D10.1 (K), U8.17 (VB2)
unnamed: C17.2, D11.1 (K), U9.17 (VB2)
unnamed: C18.2, D12.1 (K), U8.14 (VB3)
unnamed: C19.2, D13.1 (K), U9.14 (VB3)
unnamed: C25.1, D14.1 (K), R31.1, U11.3 (+), VBAT1.1 (1_1)
unnamed: Q1.4 (G), R2.2
unnamed: Q2.4 (G), R4.2
unnamed: Q3.4 (G), R6.2
unnamed: Q4.4 (G), R11.2
unnamed: Q5.4 (G), R15.2
unnamed: Q6.4 (G), R3.1
unnamed: Q7.4 (G), R5.1
unnamed: Q8.4 (G), R7.1
unnamed: Q9.4 (G), R12.1
unnamed: Q10.4 (G), R16.1
unnamed: Q11.4 (G), R14.1
unnamed: Q12.4 (G), R13.2
unnamed: Q13.4 (G), R20.1
unnamed: Q14.4 (G), R22.1
unnamed: Q15.4 (G), R19.2
unnamed: Q16.4 (G), R28.1
unnamed: Q17.4 (G), R21.2
unnamed: Q18.4 (G), R30.1
unnamed: Q19.4 (G), R27.2
unnamed: Q20.4 (G), R29.2
unnamed: Q21.4 (G), R24.1
unnamed: Q22.4 (G), R26.1
unnamed: Q23.4 (G), R23.2
unnamed: Q24.4 (G), R25.2
unnamed: C24.2, R32.1, R38.2, U1.1 (P0.1)
unnamed: C23.2, R33.1, R37.2, U1.20 (P0.2)
unnamed: C22.2, R35.1, R36.2, U1.19 (P0.3)
unnamed: U1.14 (P1.0), U2.22 (HIN1)
unnamed: U1.13 (P1.1), U2.1 (LIN1)
unnamed: U1.11 (P1.2), U2.23 (HIN2)
unnamed: U1.10 (P1.3), U2.2 (LIN2)
unnamed: U1.9 (P1.4), U2.24 (HIN3)
unnamed: U1.8 (P1.5), U2.3 (LIN3)
unnamed: R1.2, U1.5 (RSTb/C2CK)
unnamed: R2.1, U2.19 (HO1)
unnamed: R4.1, U2.16 (HO2)
unnamed: R6.1, U2.13 (HO3)
unnamed: R3.2, U2.11 (LO1)
unnamed: R5.2, U2.10 (LO2)
unnamed: R7.2, U2.9 (LO3)
unnamed: C3.2, U3.1 (CB)
unnamed: R8.1, R9.1, U3.3 (FB)
unnamed: C36.2, R41.1, R44.2, U4.1 (P0.1)
unnamed: C35.2, R40.1, R43.2, U4.20 (P0.2)
unnamed: C34.2, R39.1, R42.2, U4.19 (P0.3)
unnamed: U4.14 (P1.0), U5.22 (HIN1)
unnamed: U4.13 (P1.1), U5.1 (LIN1)
unnamed: U4.11 (P1.2), U5.23 (HIN2)
unnamed: U4.10 (P1.3), U5.2 (LIN2)
unnamed: U4.9 (P1.4), U5.24 (HIN3)
unnamed: U4.8 (P1.5), U5.3 (LIN3)
unnamed: R10.2, U4.5 (RSTb/C2CK)
unnamed: R11.1, U5.19 (HO1)
unnamed: R13.1, U5.16 (HO2)
unnamed: R15.1, U5.13 (HO3)
unnamed: R12.2, U5.11 (LO1)
unnamed: R14.2, U5.10 (LO2)
unnamed: R16.2, U5.9 (LO3)
unnamed: C41.2, R47.1, R55.2, U6.1 (P0.1)
unnamed: C39.2, R46.1, R53.2, U6.20 (P0.2)
unnamed: C37.2, R45.1, R51.2, U6.19 (P0.3)
unnamed: U6.14 (P1.0), U8.22 (HIN1)
unnamed: U6.13 (P1.1), U8.1 (LIN1)
unnamed: U6.11 (P1.2), U8.23 (HIN2)
unnamed: U6.10 (P1.3), U8.2 (LIN2)
unnamed: U6.9 (P1.4), U8.24 (HIN3)
unnamed: U6.8 (P1.5), U8.3 (LIN3)
unnamed: R17.2, U6.5 (RSTb/C2CK)
unnamed: C42.2, R50.1, R56.2, U7.1 (P0.1)
unnamed: C40.2, R49.1, R54.2, U7.20 (P0.2)
unnamed: C38.2, R48.1, R52.2, U7.19 (P0.3)
unnamed: U7.14 (P1.0), U9.22 (HIN1)
unnamed: U7.13 (P1.1), U9.1 (LIN1)
unnamed: U7.11 (P1.2), U9.23 (HIN2)
unnamed: U7.10 (P1.3), U9.2 (LIN2)
unnamed: U7.9 (P1.4), U9.24 (HIN3)
unnamed: U7.8 (P1.5), U9.3 (LIN3)
unnamed: R18.2, U7.5 (RSTb/C2CK)
unnamed: R19.1, U8.19 (HO1)
unnamed: R23.1, U8.16 (HO2)
unnamed: R27.1, U8.13 (HO3)
unnamed: R20.2, U8.11 (LO1)
unnamed: R24.2, U8.10 (LO2)
unnamed: R28.2, U8.9 (LO3)
unnamed: R21.1, U9.19 (HO1)
unnamed: R25.1, U9.16 (HO2)
unnamed: R29.1, U9.13 (HO3)
unnamed: R22.2, U9.11 (LO1)
unnamed: R26.2, U9.10 (LO2)
unnamed: R30.2, U9.9 (LO3)
